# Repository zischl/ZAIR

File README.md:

# 🐭 ZAIR - 4WD Vacuum Micromouse

A custom 4WD vacuum micromouse built for the Sri Lanka IIT Micro Maze 3.0 competition (IEEE 16×16).

The PCB also serves as the robot's structural chassis, with cutouts for the drive wheels and a central aperture for a 1020 coreless motor suction fan.

---

## 📸 PCB

|                  Top (Components)                  |                        Bottom                         |
| :------------------------------------------------: | :---------------------------------------------------: |
|  |  |

|             Traces / Silkscreen             |                  Outline & Cutouts                  |
| :-----------------------------------------: | :-------------------------------------------------: |
|  |  |

---

## ⚡ Hardware & Components

- **MCU:** STM32F405RGT6 (ARM Cortex-M4 @ 168MHz)
- **Drive Motors:** 2× Coreless 1718 motors
- **Motor Driver:** TB6612FNG breakout (red module)
- **Vacuum Fan:** Coreless 1020 motor switched by an AO3400 N-MOSFET + SS14 flyback diode
- **IMU:** LSM6DSV breakout (SPI2)
- **Encoders:** 2× MT6701 magnetic encoders (vertical 90° mounts, ABZ quadrature mode to TIM2/TIM3)
- **Sensors:** 4 active IR pairs (TEFT4300 phototransistors + SFH4545 850nm emitters, pulsed via AO3400 FETs)
- **Power:**
  - 2S LiPo (7.4V nominal)
  - MP2307 Mini360 buck converter stepped down to 3.5V for the vacuum motor
  - AMS1117-3.3 for 3.3V logic
- **Programming / Debug:** 7-pin header for SWD (`SWDIO`, `SWDCK`, `SWO`) and USART1 (`TX`, `RX`)

---

## 🛠️ PCB Specs & Files

Designed in KiCad.

- **Layers:** 2-layer FR4
- **Dimensions:** ~80mm × 115mm (1.6mm thickness, 1oz copper)
- **Silkscreen:** White

### Files

- **KiCad Project:** `hardware/schematic/ZAIR/`
- **Schematic PDF:** [`hardware/schematic/ZAIR/ZAIR_Schematic.pdf`](hardware/schematic/ZAIR/ZAIR_Schematic.pdf)
- **Gerbers:** [`hardware/schematic/ZAIR/gerbers/`](hardware/schematic/ZAIR/gerbers/)
- **BOM:** [`hardware/schematic/ZAIR/ZAIR.csv`](hardware/schematic/ZAIR/ZAIR.csv)

---

## ⚙️ Drivetrain CAD

Designed in Onshape. A 3-gear direct-drive setup where the central Coreless 1718 motor pinion meshes simultaneously with both geared wheels.

|                     3-Gear Mesh                     |                   Drivetrain Assembly                   |
| :-------------------------------------------------: | :-----------------------------------------------------: |
|  |  |

### STEP Models (`hardware/cad/`)

- **Motor:** Coreless 1718 ([`hardware/cad/motor_1718.step`](hardware/cad/motor_1718.step))
- **Wheel:** 22mm Geared Wheel ([`hardware/cad/geared_wheel.step`](hardware/cad/geared_wheel.step))
- **Mount:** Drivetrain motor mount bracket ([`hardware/cad/drivetrain_mount.step`](hardware/cad/drivetrain_mount.step))

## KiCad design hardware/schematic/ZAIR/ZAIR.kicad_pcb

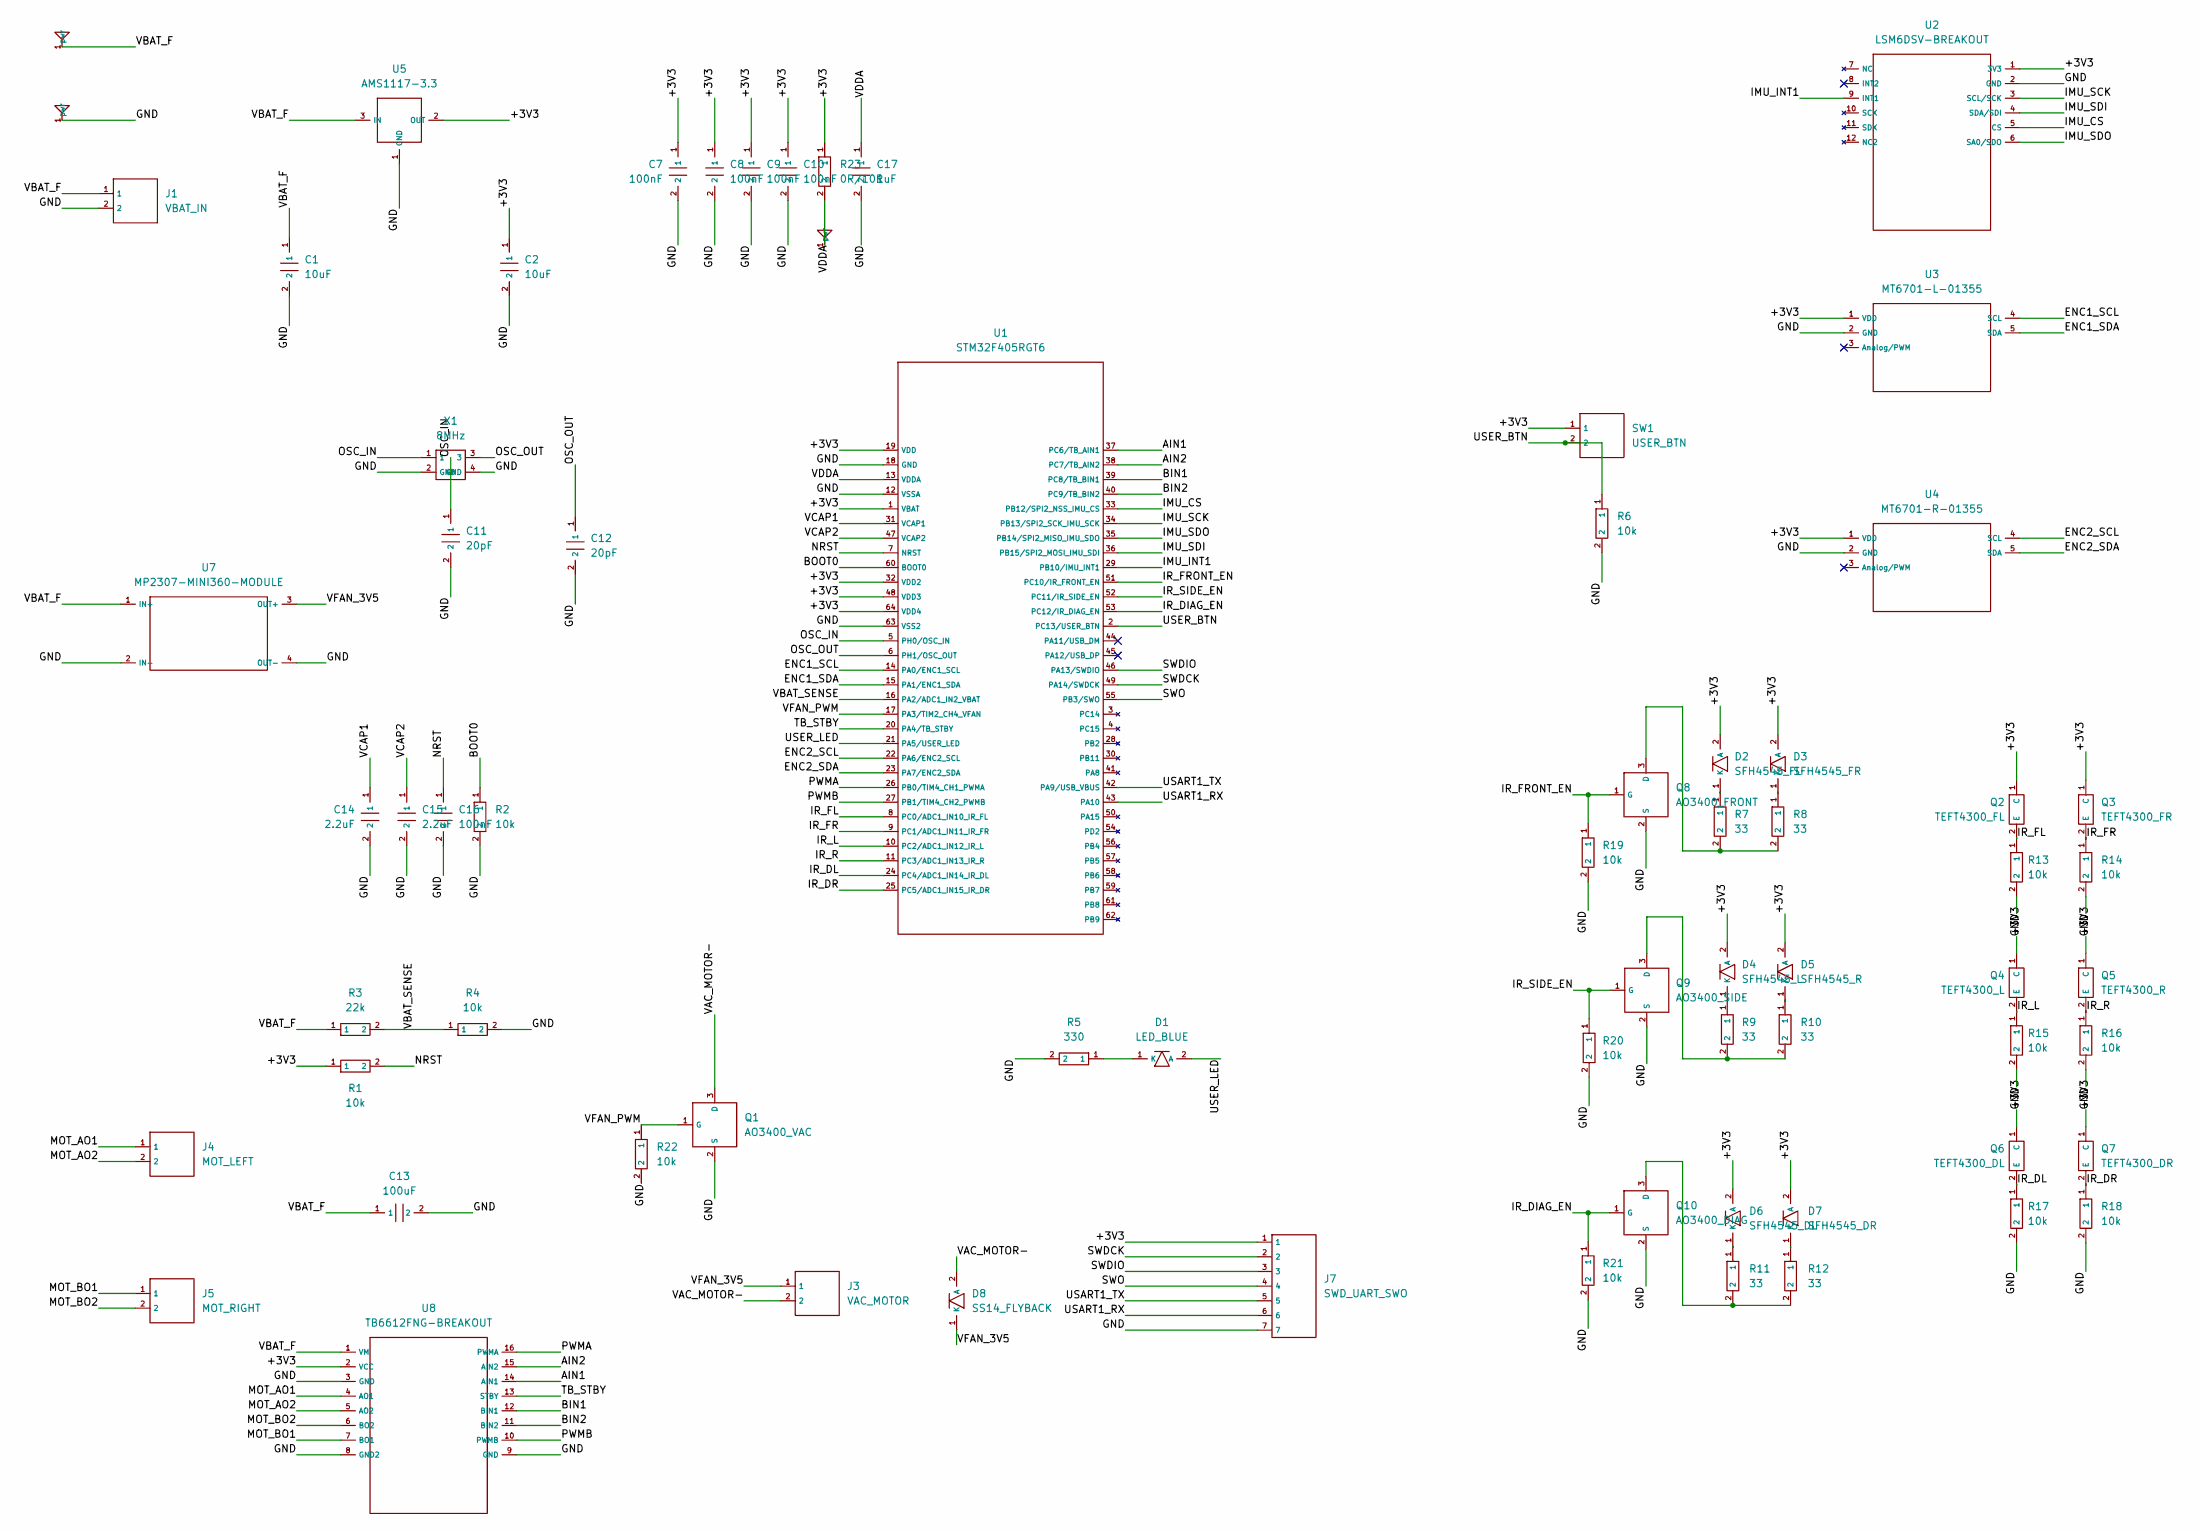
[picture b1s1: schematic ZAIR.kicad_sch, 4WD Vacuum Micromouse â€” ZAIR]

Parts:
C1, C2: 10uF; C_0603_1608Metric
C7, C8, C9, C10, C16: 100nF; C_0603_1608Metric
C11, C12: 20pF; C_0603_1608Metric
C13: 100uF; CP_Elec_6.3x5.4
C14, C15: 2.2uF; C_0603_1608Metric
C17: 1uF; C_0603_1608Metric
D1: LED_BLUE; LED_0603_1608Metric
D2: SFH4545_FL; LED_D3.0mm
D3: SFH4545_FR; LED_D3.0mm
D4: SFH4545_L; LED_D3.0mm
D5: SFH4545_R; LED_D3.0mm
D6: SFH4545_DL; LED_D3.0mm
D7: SFH4545_DR; LED_D3.0mm
D8: SS14_FLYBACK; D_SMA
J1: VBAT_IN; PinHeader_1x02_P2.54mm_Vertical
J3: VAC_MOTOR; PinHeader_1x02_P2.54mm_Vertical
J4: MOT_LEFT; PinHeader_1x02_P2.54mm_Vertical
J5: MOT_RIGHT; PinHeader_1x02_P2.54mm_Vertical
J7: SWD_UART_SWO; PinHeader_1x07_P2.54mm_Vertical
Q1: AO3400_VAC; SOT-23
Q2: TEFT4300_FL; LED_D3.0mm
Q3: TEFT4300_FR; LED_D3.0mm
Q4: TEFT4300_L; LED_D3.0mm
Q5: TEFT4300_R; LED_D3.0mm
Q6: TEFT4300_DL; LED_D3.0mm
Q7: TEFT4300_DR; LED_D3.0mm
Q8: AO3400_FRONT; SOT-23
Q9: AO3400_SIDE; SOT-23
Q10: AO3400_DIAG; SOT-23
R1, R2, R4, R6, R13, R14, R15, R16, R17, R18, R19, R20, R21, R22: 10k; R_0603_1608Metric
R3: 22k; R_0603_1608Metric
R5: 330; R_0603_1608Metric
R7, R8, R9, R10, R11, R12: 33; R_0603_1608Metric
R23: 0R/10R; R_0603_1608Metric
SW1: USER_BTN; PinHeader_1x02_P2.54mm_Vertical
U1: STM32F405RGT6; LQFP-64_10x10mm_P0.5mm
U2: LSM6DSV-BREAKOUT; LSM6DSV_Breakout
U3: MT6701-L-01355; MT6701_Breakout
U4: MT6701-R-01355; MT6701_Breakout
U5: AMS1117-3.3; SOT-223-3_TabPin2
U7: MP2307-MINI360-MODULE; MP2307_Mini360_Buck
U8: TB6612FNG-BREAKOUT; TB6612FNG_Breakout_Red
X1: 8MHz; Crystal_SMD_3225-4Pin_3.2x2.5mm

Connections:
/+3V3: C2.1, C7.1, C8.1, C9.1, C10.1, D2.2 (A), D3.2 (A), D4.2 (A), D5.2 (A), D6.2 (A), D7.2 (A), J7.1, Q2.1 (C), Q3.1 (C), Q4.1 (C), Q5.1 (C), Q6.1 (C), Q7.1 (C), R1.1, R23.1, SW1.1, U1.1 (VBAT), U1.19 (VDD), U1.32 (VDD2), U1.48 (VDD3), U1.64 (VDD4), U2.1 (3V3), U3.1 (VDD), U4.1 (VDD), U5.2 (OUT), U8.2 (VCC)
/AIN1: U1.37 (PC6/TB_AIN1), U8.14 (AIN1)
/AIN2: U1.38 (PC7/TB_AIN2), U8.15 (AIN2)
/BIN1: U1.39 (PC8/TB_BIN1), U8.12 (BIN1)
/BIN2: U1.40 (PC9/TB_BIN2), U8.11 (BIN2)
/BOOT0: R2.1, U1.60 (BOOT0)
/ENC1_SCL: U1.14 (PA0/ENC1_SCL), U3.4 (SCL)
/ENC1_SDA: U1.15 (PA1/ENC1_SDA), U3.5 (SDA)
/ENC2_SCL: U1.22 (PA6/ENC2_SCL), U4.4 (SCL)
/ENC2_SDA: U1.23 (PA7/ENC2_SDA), U4.5 (SDA)
/IMU_CS: U1.33 (PB12/SPI2_NSS_IMU_CS), U2.5 (CS)
/IMU_INT1: U1.29 (PB10/IMU_INT1), U2.9 (INT1)
/IMU_SCK: U1.34 (PB13/SPI2_SCK_IMU_SCK), U2.3 (SCL/SCK)
/IMU_SDI: U1.36 (PB15/SPI2_MOSI_IMU_SDI), U2.4 (SDA/SDI)
/IMU_SDO: U1.35 (PB14/SPI2_MISO_IMU_SDO), U2.6 (SA0/SDO)
/IR_DIAG_EN: Q10.1 (G), R21.1, U1.53 (PC12/IR_DIAG_EN)
/IR_DL: Q6.2 (E), R17.1, U1.24 (PC4/ADC1_IN14_IR_DL)
/IR_DR: Q7.2 (E), R18.1, U1.25 (PC5/ADC1_IN15_IR_DR)
/IR_FL: Q2.2 (E), R13.1, U1.8 (PC0/ADC1_IN10_IR_FL)
/IR_FR: Q3.2 (E), R14.1, U1.9 (PC1/ADC1_IN11_IR_FR)
/IR_FRONT_EN: Q8.1 (G), R19.1, U1.51 (PC10/IR_FRONT_EN)
/IR_L: Q4.2 (E), R15.1, U1.10 (PC2/ADC1_IN12_IR_L)
/IR_R: Q5.2 (E), R16.1, U1.11 (PC3/ADC1_IN13_IR_R)
/IR_SIDE_EN: Q9.1 (G), R20.1, U1.52 (PC11/IR_SIDE_EN)
/MOT_AO1: J4.1, U8.4 (AO1)
/MOT_AO2: J4.2, U8.5 (AO2)
/MOT_BO1: J5.1, U8.7 (BO1)
/MOT_BO2: J5.2, U8.6 (BO2)
/NRST: C16.1, R1.2, U1.7 (NRST)
/OSC_IN: C11.1, U1.5 (PH0/OSC_IN), X1.1
/OSC_OUT: C12.1, U1.6 (PH1/OSC_OUT), X1.3
/PWMA: U1.26 (PB0/TIM4_CH1_PWMA), U8.16 (PWMA)
/PWMB: U1.27 (PB1/TIM4_CH2_PWMB), U8.10 (PWMB)
/SWDCK: J7.2, U1.49 (PA14/SWDCK)
/SWDIO: J7.3, U1.46 (PA13/SWDIO)
/SWO: J7.4, U1.55 (PB3/SWO)
/TB_STBY: U1.20 (PA4/TB_STBY), U8.13 (STBY)
/USART1_RX: J7.6, U1.43 (PA10)
/USART1_TX: J7.5, U1.42 (PA9/USB_VBUS)
/USER_BTN: R6.1, SW1.2, U1.2 (PC13/USER_BTN)
/USER_LED: D1.2 (A), U1.21 (PA5/USER_LED)
/VAC_MOTOR-: D8.2 (A), J3.2, Q1.3 (D)
/VBAT_SENSE: R3.2, R4.1, U1.16 (PA2/ADC1_IN2_VBAT)
/VCAP1: C14.1, U1.31 (VCAP1)
/VCAP2: C15.1, U1.47 (VCAP2)
/VFAN_3V5: D8.1 (K), J3.1, U7.3 (OUT+)
/VFAN_PWM: Q1.1 (G), R22.1, U1.17 (PA3/TIM2_CH4_VFAN)
unnamed: D1.1 (K), R5.1
unnamed: D2.1 (K), R7.1
unnamed: D3.1 (K), R8.1
unnamed: D4.1 (K), R9.1
unnamed: D5.1 (K), R10.1
unnamed: D6.1 (K), R11.1
unnamed: D7.1 (K), R12.1
unnamed: Q8.3 (D), R7.2, R8.2
unnamed: Q9.3 (D), R9.2, R10.2
unnamed: Q10.3 (D), R11.2, R12.2

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
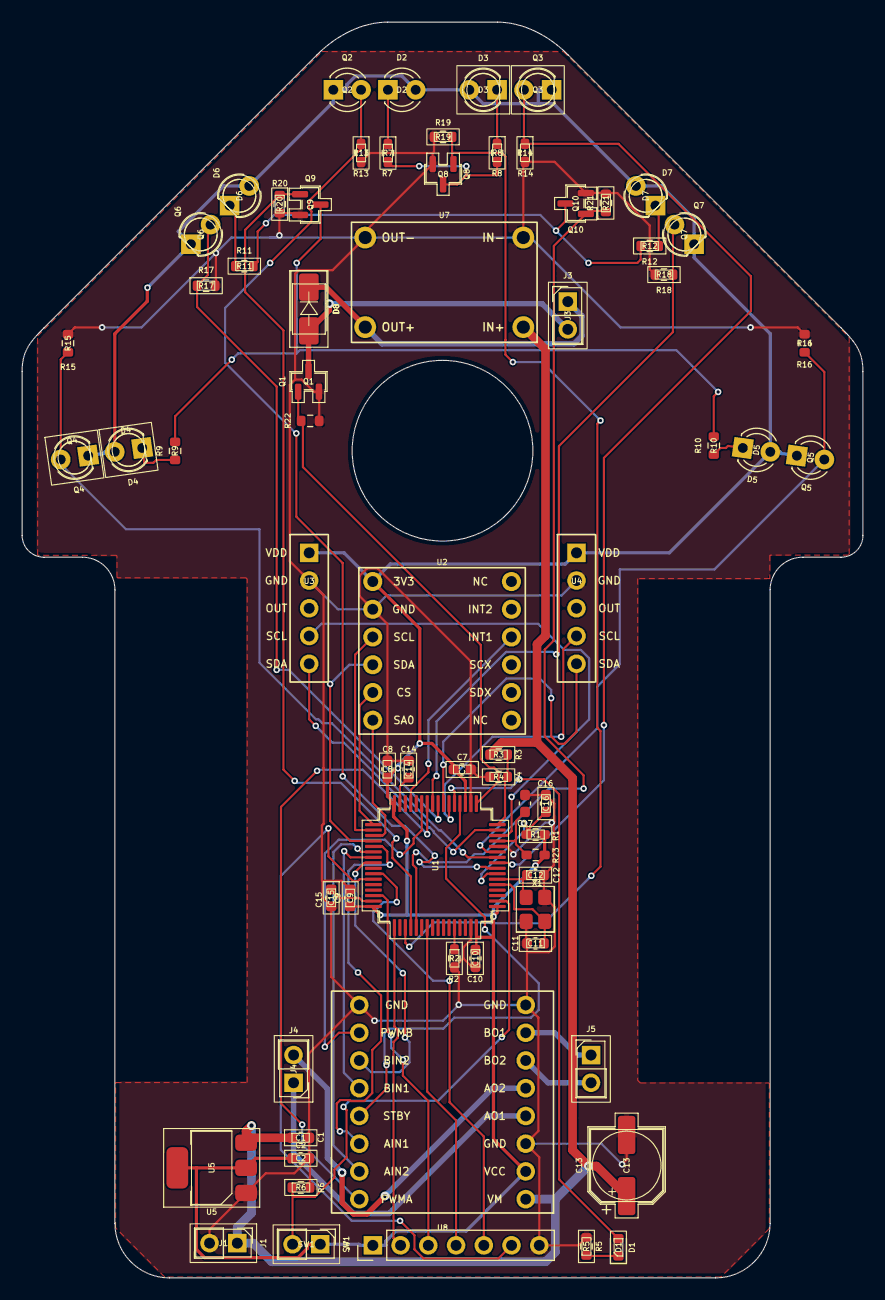
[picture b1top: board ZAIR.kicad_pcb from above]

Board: 2 copper layers, 77.0 x 115.0 mm, 68 parts (0 on the bottom side), 60 nets.
